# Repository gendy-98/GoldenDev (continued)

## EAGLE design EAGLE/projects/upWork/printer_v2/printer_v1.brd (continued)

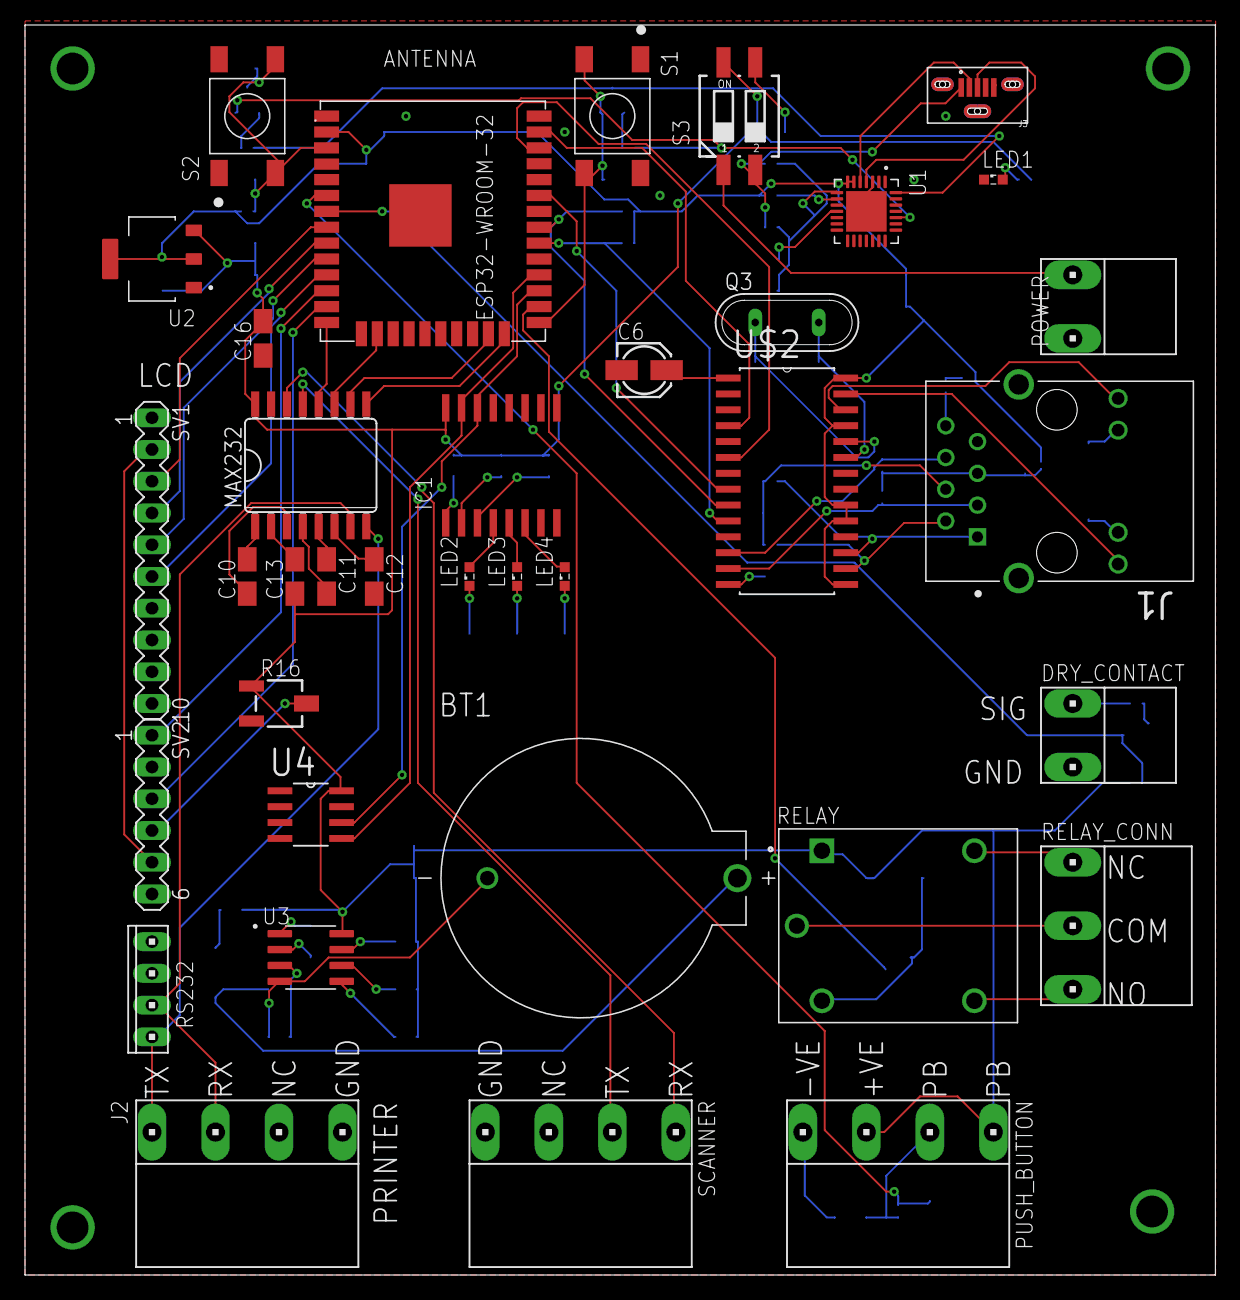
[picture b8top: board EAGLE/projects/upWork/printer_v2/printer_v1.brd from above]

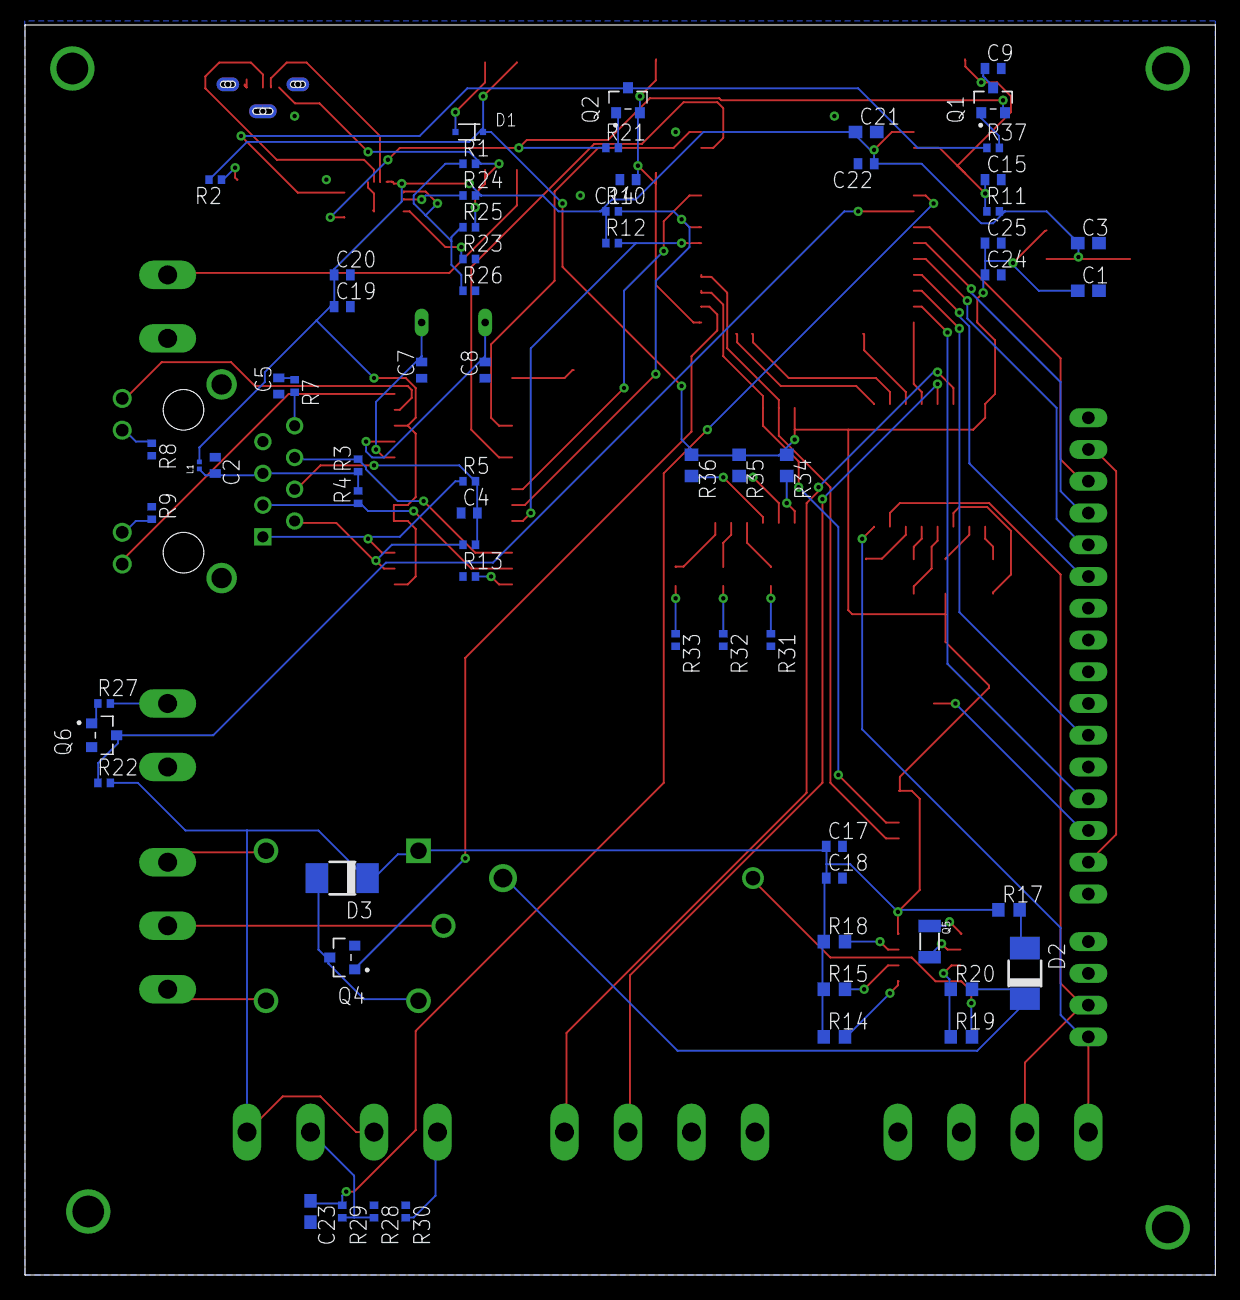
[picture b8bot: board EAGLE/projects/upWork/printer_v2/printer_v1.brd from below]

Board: 2 copper layers, 95.2 x 100.0 mm, 100 parts (64 on the bottom side), 92 nets.

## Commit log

2023-04-15 remove extern "C"
2023-07-22 adding eagle files
2023-07-22 small main modifications
2023-08-26 fix a bug in printer uart
2023-09-30 Enable fullDuplex
2026-04-22 starting refactoring
